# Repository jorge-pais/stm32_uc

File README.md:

# stm32_uc
Simple microcontroller board built around a STM32F103

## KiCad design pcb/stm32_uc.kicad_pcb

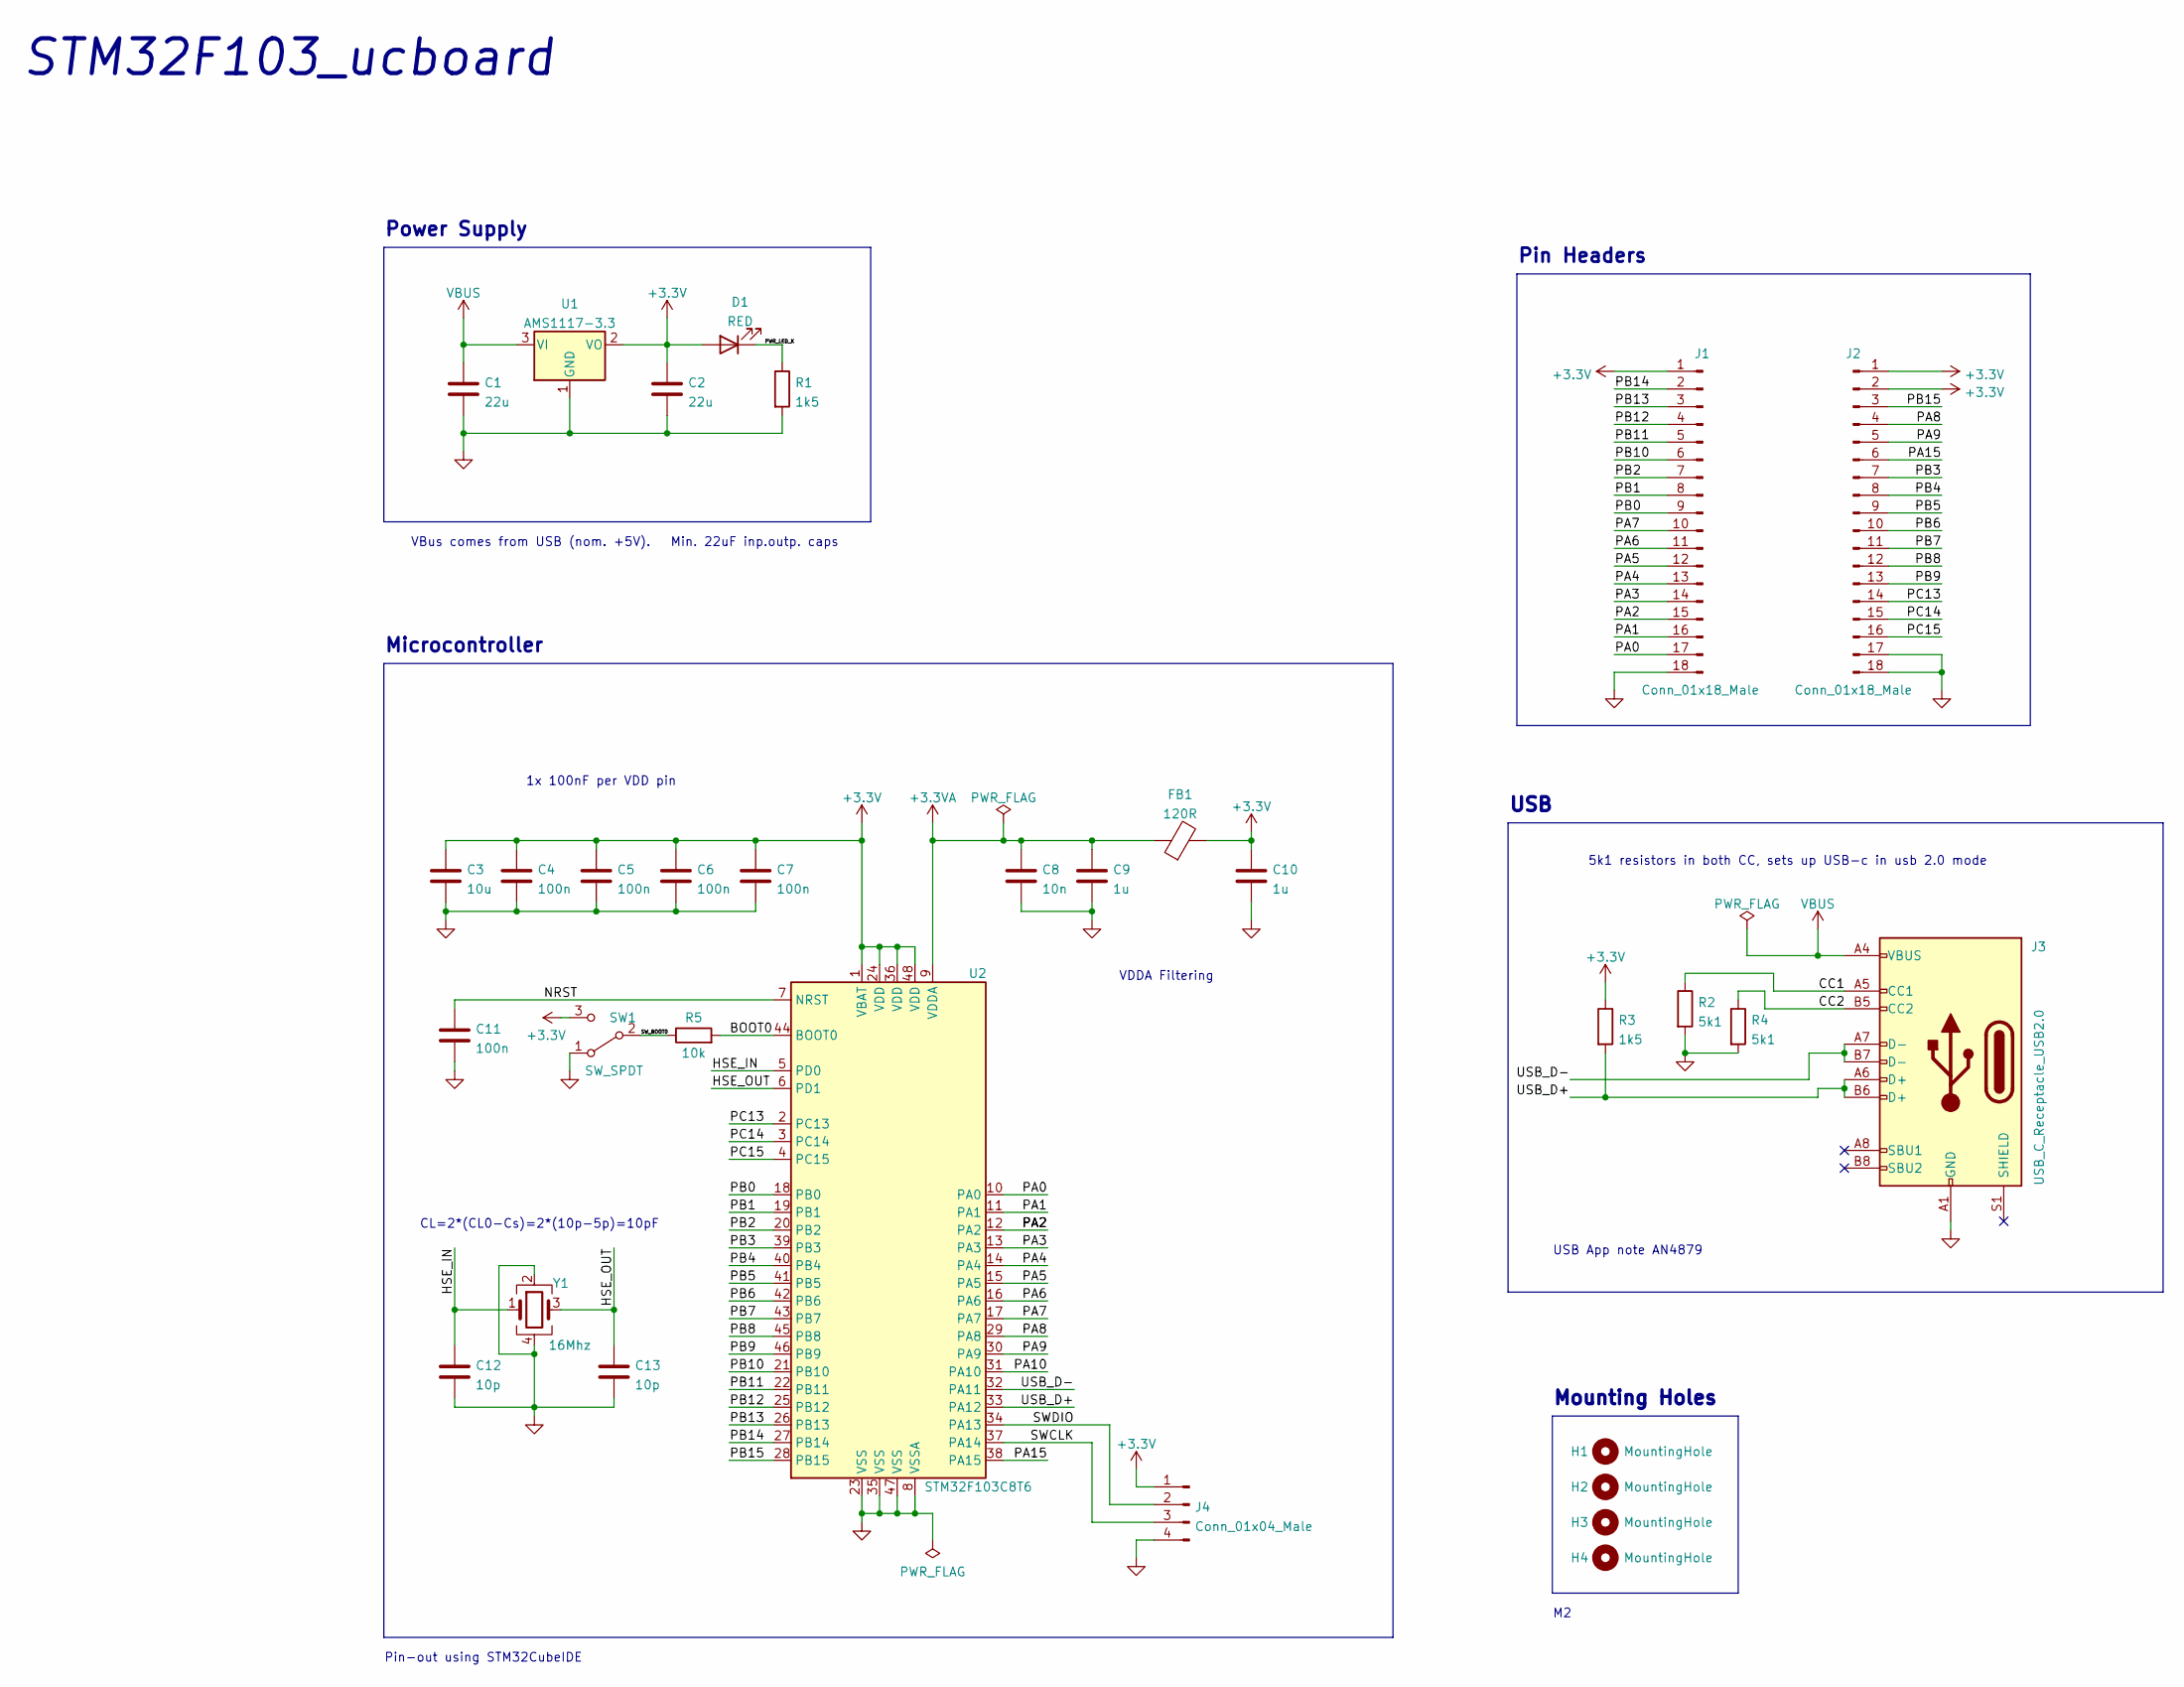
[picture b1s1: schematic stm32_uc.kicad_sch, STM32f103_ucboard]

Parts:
C1, C2: 22u; C_0805_2012Metric
C3: 10u; C_0603_1608Metric
C4, C5, C6, C7, C11: 100n; C_0402_1005Metric
C8: 10n; C_0402_1005Metric
C9, C10: 1u; C_0402_1005Metric
C12, C13: 10p; C_0402_1005Metric
D1: RED; LED_0603_1608Metric
FB1: 120R; L_0603_1608Metric
H1, H2, H3, H4: MountingHole; MountingHole_2.2mm_M2
J1, J2: Conn_01x18_Male; PinHeader_1x18_P2.54mm_Vertical
J3: USB_C_Receptacle_USB2.0; USB_C_Receptacle_GCT_USB4085
J4: Conn_01x04_Male; PinHeader_1x04_P2.54mm_Vertical
R1, R3: 1k5; R_0402_1005Metric
R2, R4: 5k1; R_0402_1005Metric
R5: 10k; R_0402_1005Metric
SW1: SW_SPDT; SW_SPDT_PCM12
U1: AMS1117-3.3; SOT-223-3_TabPin2
U2: STM32F103C8T6; LQFP-48_7x7mm_P0.5mm
Y1: 16Mhz; Crystal_SMD_3225-4Pin_3.2x2.5mm

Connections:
+3.3VA: C8.1, C9.1, FB1.1, U2.9 (VDDA)
+3V3: C2.1, C3.1, C4.1, C5.1, C6.1, C7.1, C10.1, D1.2 (A), FB1.2, J1.1, J2.1, J2.2, J4.1, R3.1, SW1.3 (C), U1.2 (VO), U2.1 (VBAT), U2.24 (VDD), U2.36 (VDD), U2.48 (VDD)
/BOOT0: R5.2, U2.44 (BOOT0)
/CC1: J3.A5 (CC1), R2.1
/CC2: J3.B5 (CC2), R4.1
/HSE_IN: C12.1, U2.5 (PD0), Y1.1
/HSE_OUT: C13.1, U2.6 (PD1), Y1.3
/NRST: C11.1, U2.7 (NRST)
/PA0: J1.17, U2.10 (PA0)
/PA1: J1.16, U2.11 (PA1)
/PA2: J1.15, U2.12 (PA2)
/PA3: J1.14, U2.13 (PA3)
/PA4: J1.13, U2.14 (PA4)
/PA5: J1.12, U2.15 (PA5)
/PA6: J1.11, U2.16 (PA6)
/PA7: J1.10, U2.17 (PA7)
/PA8: J2.4, U2.29 (PA8)
/PA9: J2.5, U2.30 (PA9)
/PA10: U2.31 (PA10)
/PA15: J2.6, U2.38 (PA15)
/PB0: J1.9, U2.18 (PB0)
/PB1: J1.8, U2.19 (PB1)
/PB2: J1.7, U2.20 (PB2)
/PB3: J2.7, U2.39 (PB3)
/PB4: J2.8, U2.40 (PB4)
/PB5: J2.9, U2.41 (PB5)
/PB6: J2.10, U2.42 (PB6)
/PB7: J2.11, U2.43 (PB7)
/PB8: J2.12, U2.45 (PB8)
/PB9: J2.13, U2.46 (PB9)
/PB10: J1.6, U2.21 (PB10)
/PB11: J1.5, U2.22 (PB11)
/PB12: J1.4, U2.25 (PB12)
/PB13: J1.3, U2.26 (PB13)
/PB14: J1.2, U2.27 (PB14)
/PB15: J2.3, U2.28 (PB15)
/PC13: J2.14, U2.2 (PC13)
/PC14: J2.15, U2.3 (PC14)
/PC15: J2.16, U2.4 (PC15)
/PWR_LED_K: D1.1 (K), R1.1
/SWCLK: J4.3, U2.37 (PA14)
/SWDIO: J4.2, U2.34 (PA13)
/SW_BOOT0: R5.1, SW1.2 (B)
/USB_D+: J3.A6 (D+), J3.B6 (D+), R3.2, U2.33 (PA12)
/USB_D-: J3.A7 (D-), J3.B7 (D-), U2.32 (PA11)
GND: C1.2, C2.2, C3.2, C4.2, C5.2, C6.2, C7.2, C8.2, C9.2, C10.2, C11.2, C12.2, C13.2, J1.18, J2.17, J2.18, J3.A1 (GND), J3.A12 (GND), J3.B1 (GND), J3.B12 (GND), J4.4, R1.2, R2.2, R4.2, SW1.1 (A), U1.1 (GND), U2.8 (VSSA), U2.23 (VSS), U2.35 (VSS), U2.47 (VSS), Y1.2, Y1.4
VBUS: C1.1, J3.A4 (VBUS), J3.A9 (VBUS), J3.B4 (VBUS), J3.B9 (VBUS), U1.3 (VI)

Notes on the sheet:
Microcontroller
Pin Headers
1x 100nF per VDD pin
STM32F103_ucboard
VBus comes from USB (nom. +5V). Min. 22uF inp.outp. caps
USB
5k1 resistors in both CC, sets up USB-c in usb 2.0 mode
Mounting Holes
Pin-out using STM32CubeIDE
CL=2*(CL0-Cs)=2*(10p-5p)=10pF
VDDA Filtering
USB App note AN4879
Power Supply

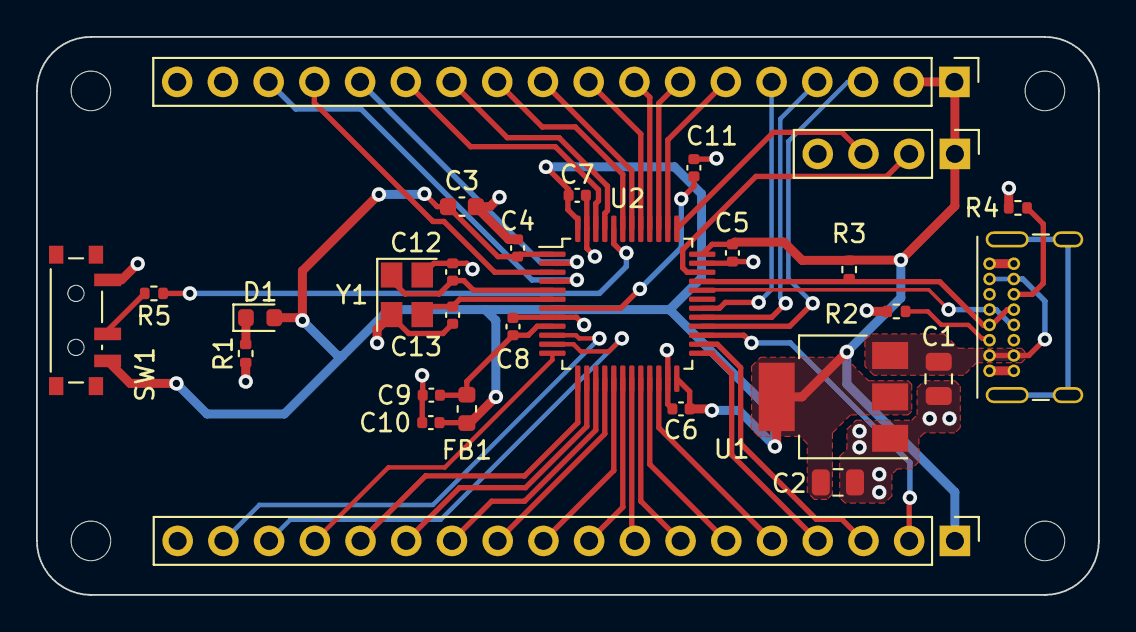
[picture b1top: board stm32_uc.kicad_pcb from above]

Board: 2 copper layers, 59.0 x 31.0 mm, 32 parts (0 on the bottom side), 46 nets.

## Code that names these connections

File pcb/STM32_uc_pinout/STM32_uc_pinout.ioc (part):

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Mcu.Name=STM32F103C(8-B)Tx
Mcu.Package=LQFP48
Mcu.UserName=STM32F103C8Tx
PA11.Mode=Device
PA11.Signal=USB_DM
PA12.Mode=Device
PA12.Signal=USB_DP
PA13.Mode=Serial_Wire
PA13.Signal=SYS_JTMS-SWDIO
PA14.Mode=Serial_Wire
PA14.Signal=SYS_JTCK-SWCLK
PD0-OSC_IN.Mode=HSE-External-Oscillator
PD0-OSC_IN.Signal=RCC_OSC_IN
PD1-OSC_OUT.Mode=HSE-External-Oscillator
PD1-OSC_OUT.Signal=RCC_OSC_OUT
board=custom

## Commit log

2022-01-30 updated pdb
2022-01-31 update schematic + application notes
2022-01-31 added power circuitry
2022-02-02 added uc pin labels
2022-02-02 started adding connectors
2022-02-02 finished connectors
2022-02-03 started anotating schematic
2022-02-08 moved schematic/pcb files
2022-02-08 fix pin header pinout
2022-02-08 removed kicad backup folder
2022-02-08 finished rough layout
2022-02-09 signal routing
2022-02-09 more signal routing, started power routing
2022-02-12 finished routing
2022-02-12 added schematic pdf
2022-02-20 started on usb b version
2022-04-13 Added LICENSE:md
